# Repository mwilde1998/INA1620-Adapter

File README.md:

# INA1620 to OPA1688 Adapter
## Overview
This project is a simple adapter board for adapting the INA1620 opamp to the pinout used by the OPA1688 opamp. I made this project as a modification to my Topping NX4 DSD portable headphone amplifier, since the INA1620 is a technically superior opamp that looks to be a suitable upgrade over the OPA1688 opamps in the final amplification stage of the NX4. 

The PCB design essentially matches up the pinout of the OPA1688 to the equivalent pins on the INA1620, with a couple of 0.1uF capacitors added between GND and the voltage rails for the purpose of noise surpression, as suggested by the application notes for the INA1620 from Texas Instruments.
## Project Status Updates
**3/22/20:** Final design complete. Prototype PCBs ordered from OSH Park, stencils ordered from OSH Stencils

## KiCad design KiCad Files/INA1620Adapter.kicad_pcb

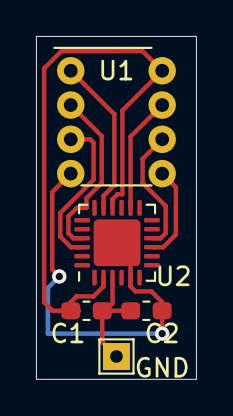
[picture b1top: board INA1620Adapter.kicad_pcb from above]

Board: 2 copper layers, 8.9 x 19.1 mm, 5 parts (0 on the bottom side), 9 nets.

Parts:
C1, C2: 0.1uF; C_0603_1608Metric_Pad1.05x0.95mm_HandSolder
GND: TestPoint; TestPoint_THTPad_1.5x1.5mm_Drill0.7mm
U1: OPA1688_CSTM; OPA1688
U2: INA1620; WQFN-24-1EP_4x4mm_P0.5mm_EP2.6x2.6mm

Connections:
unnamed: C1.1, U1.8, U2.2, U2.16
unnamed: C1.2, C2.1, GND.1, U2.3
unnamed: C2.2, U1.4, U2.5, U2.25
unnamed: U1.1, U2.17
unnamed: U1.2, U2.21
unnamed: U1.3, U2.22
unnamed: U1.5, U2.9
unnamed: U1.6, U2.10
unnamed: U1.7, U2.14

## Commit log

2020-03-25 Committed all KiCad Files
2020-03-25 Update README.md
    README updated with a project description and status update.
2020-03-25 Image of PCB ordered from OSH Park for the README
2020-03-26 Update README.md
    Added image of PCB
2020-03-26 Update README.md
    Fixed typo in image
